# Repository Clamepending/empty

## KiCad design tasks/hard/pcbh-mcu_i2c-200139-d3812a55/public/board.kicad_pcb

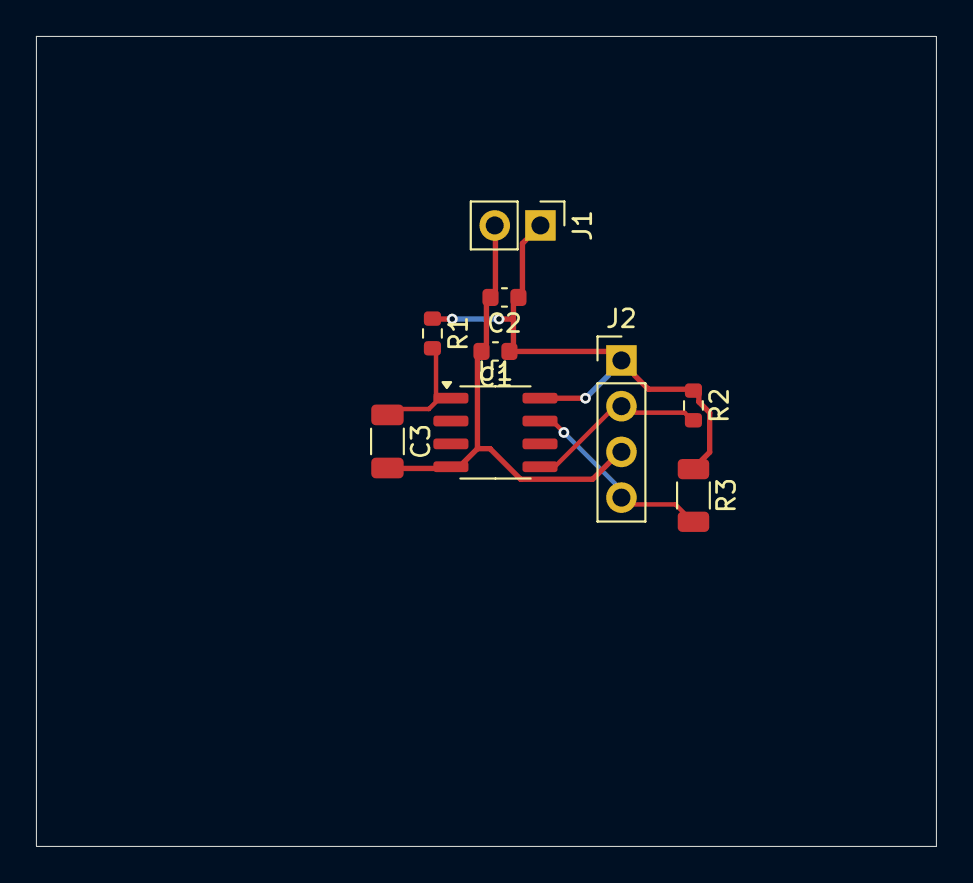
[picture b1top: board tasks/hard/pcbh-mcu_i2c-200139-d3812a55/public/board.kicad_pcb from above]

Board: 2 copper layers, 50.0 x 45.0 mm, 9 parts (0 on the bottom side), 5 nets.

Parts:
C1: 100n; C_0603_1608Metric
C2: 4.7u; C_0603_1608Metric
C3: 220n; C_1206_3216Metric
J1: PinHeader_1x02_P2.54mm_Vertical
J2: PinHeader_1x04_P2.54mm_Vertical
R1: 15; R_0603_1608Metric
R2: 5.1k; R_0603_1608Metric
R3: 5.1k; R_1206_3216Metric
U1: SOIC-8_3.9x4.9mm_P1.27mm

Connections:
+5V: C1.1, C2.1, J1.1, J2.1, R1.1, R2.1, R3.1, U1.8
GND: C1.2, C2.2, C3.2, J1.2, J2.3, U1.4
NRST: C3.1, R1.2, U1.1
SCL: J2.4, R3.2, U1.7
SDA: J2.2, R2.2, U1.5

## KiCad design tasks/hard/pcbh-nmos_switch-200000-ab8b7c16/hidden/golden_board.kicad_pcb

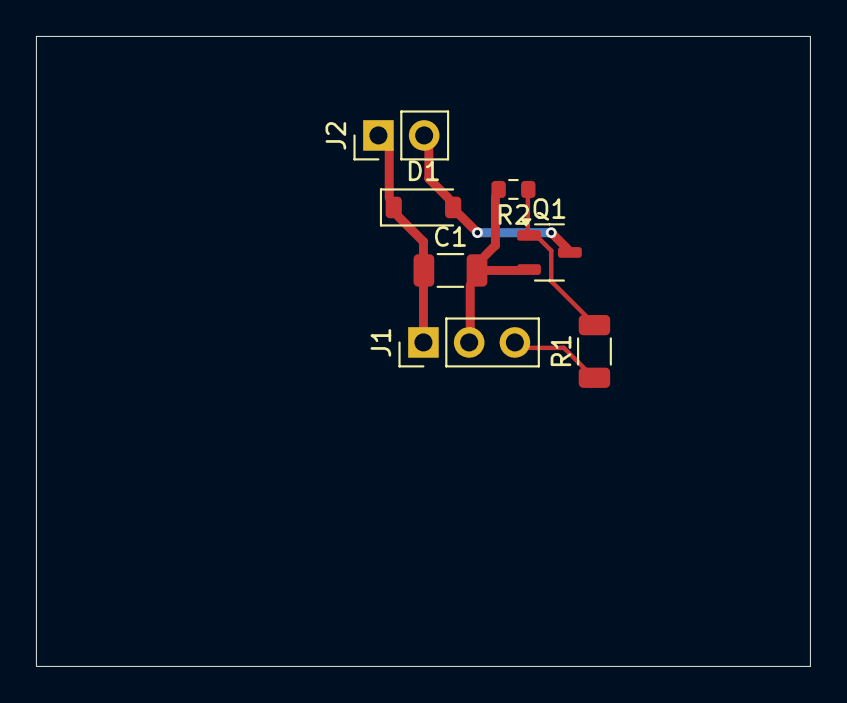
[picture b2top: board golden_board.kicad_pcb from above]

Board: 2 copper layers, 43.0 x 35.0 mm, 7 parts (0 on the bottom side), 5 nets.

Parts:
C1: 6.8u; C_1206_3216Metric
D1: D_SOD-123
J1: PinHeader_1x03_P2.54mm_Vertical
J2: PinHeader_1x02_P2.54mm_Vertical
Q1: SOT-23-3
R1: 91; R_1206_3216Metric
R2: 24k; R_0603_1608Metric

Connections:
+9V: C1.1, D1.1, J1.1, J2.1
CTRL: J1.3, R1.1
GATE: Q1.1, R1.2, R2.1
GND: C1.2, J1.2, Q1.2, R2.2
SW: D1.2, J2.2, Q1.3

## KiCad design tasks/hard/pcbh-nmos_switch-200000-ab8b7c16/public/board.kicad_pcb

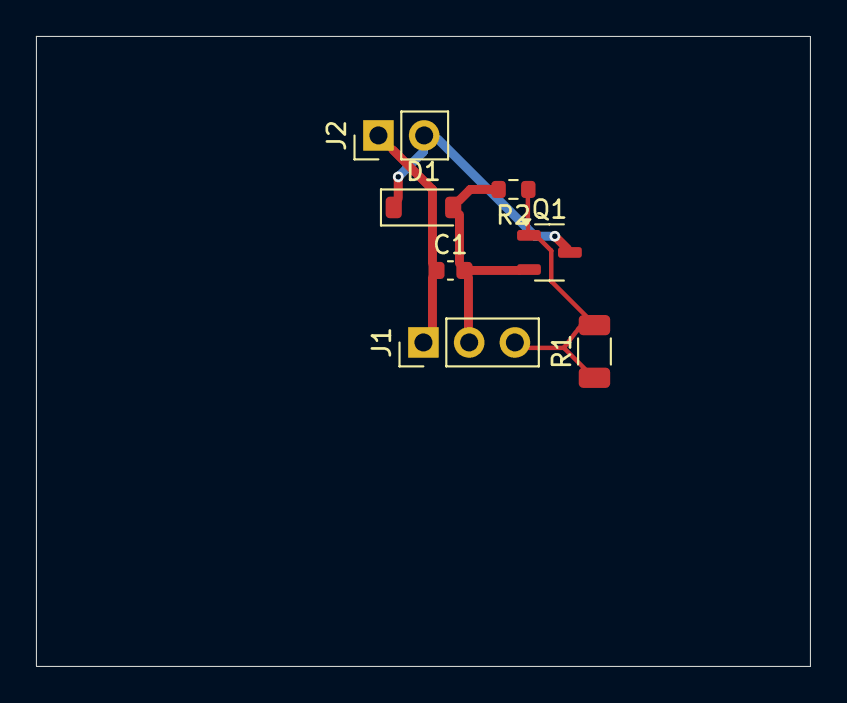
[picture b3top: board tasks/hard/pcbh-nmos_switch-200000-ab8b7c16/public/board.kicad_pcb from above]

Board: 2 copper layers, 43.0 x 35.0 mm, 7 parts (0 on the bottom side), 5 nets.

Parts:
C1: 6.8u; C_0603_1608Metric
D1: D_SOD-123
J1: PinHeader_1x03_P2.54mm_Vertical
J2: PinHeader_1x02_P2.54mm_Vertical
Q1: SOT-23-3
R1: 91; R_1206_3216Metric
R2: 24k; R_0603_1608Metric

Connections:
+9V: C1.1, J1.1, J2.1
CTRL: J1.3, R1.1
GATE: Q1.1, R1.2, R2.1
GND: C1.2, D1.2, J1.2, Q1.2, R2.2
SW: D1.1, J2.2, Q1.3

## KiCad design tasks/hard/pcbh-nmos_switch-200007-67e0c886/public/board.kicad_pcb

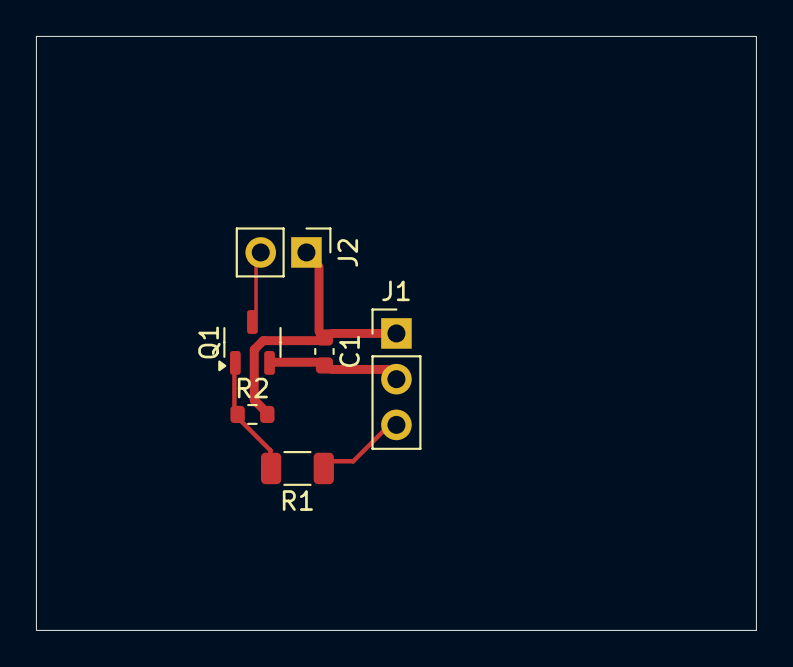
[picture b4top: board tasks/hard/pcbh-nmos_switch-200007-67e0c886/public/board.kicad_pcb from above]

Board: 2 copper layers, 40.0 x 33.0 mm, 6 parts (0 on the bottom side), 5 nets.

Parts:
C1: 1.5u; C_0603_1608Metric
J1: PinHeader_1x03_P2.54mm_Vertical
J2: PinHeader_1x02_P2.54mm_Vertical
Q1: SOT-23-3
R1: 43; R_1206_3216Metric
R2: 11k; R_0603_1608Metric

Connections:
+12V: C1.1, J1.1, J2.1, R2.2
CTRL: J1.3, R1.1
GATE: Q1.1, R1.2, R2.1
GND: C1.2, J1.2, Q1.2
SW: J2.2, Q1.3
